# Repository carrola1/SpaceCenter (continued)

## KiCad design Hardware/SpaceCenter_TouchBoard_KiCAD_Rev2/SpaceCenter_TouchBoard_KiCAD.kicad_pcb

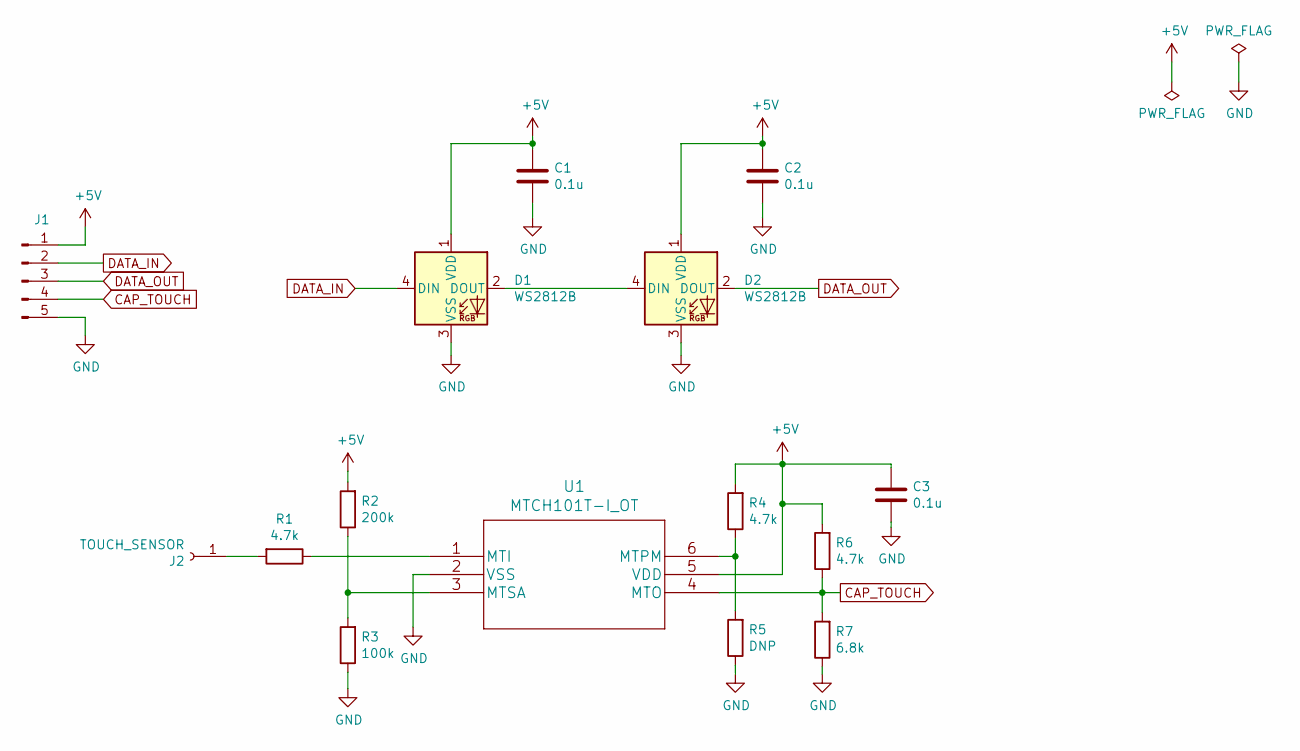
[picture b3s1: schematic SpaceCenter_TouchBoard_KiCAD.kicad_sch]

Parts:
C1, C2, C3: 0.1u; C_0402_1005Metric_Pad0.74x0.62mm_HandSolder
D1, D2: WS2812B; LED_WS2812B_PLCC4_5.0x5.0mm_P3.2mm
J1: Conn_01x05_Male; JST_SH_BM05B-SRSS-TB_1x05-1MP_P1.00mm_Vertical
J2: TOUCH_SENSOR; SolderWirePad_1x01_SMD_5x10mm
R1, R4, R6: 4.7k; R_0402_1005Metric_Pad0.72x0.64mm_HandSolder
R2: 200k; R_0402_1005Metric_Pad0.72x0.64mm_HandSolder
R3: 100k; R_0402_1005Metric_Pad0.72x0.64mm_HandSolder
R5: DNP; R_0402_1005Metric_Pad0.72x0.64mm_HandSolder
R7: 6.8k; R_0402_1005Metric_Pad0.72x0.64mm_HandSolder
U1: MTCH101T-I_OT; MTCH101T-I&slash_OT

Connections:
+5V: C1.1, C2.1, C3.1, D1.1 (VDD), D2.1 (VDD), J1.1, R2.2, R4.2, R6.2, U1.5 (VDD)
CAP_TOUCH: J1.4, R6.1, R7.2, U1.4 (MTO)
DATA_IN: D1.4 (DIN), J1.2
DATA_OUT: D2.2 (DOUT), J1.3
GND: C1.2, C2.2, C3.2, D1.3 (VSS), D2.3 (VSS), J1.5, R3.1, R5.1, R7.1, U1.2 (VSS)
unnamed: D1.2 (DOUT), D2.4 (DIN)
unnamed: J2.1, R1.2
unnamed: R1.1, U1.1 (MTI)
unnamed: R2.1, R3.2, U1.3 (MTSA)
unnamed: R4.1, R5.2, U1.6 (MTPM)

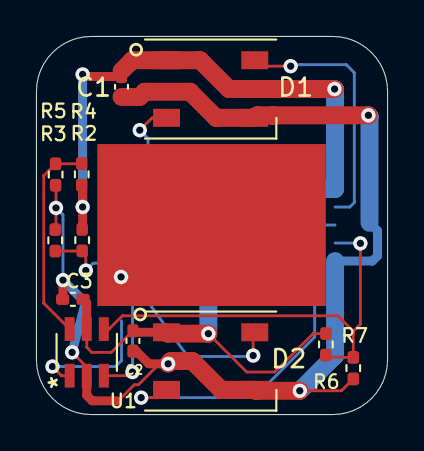
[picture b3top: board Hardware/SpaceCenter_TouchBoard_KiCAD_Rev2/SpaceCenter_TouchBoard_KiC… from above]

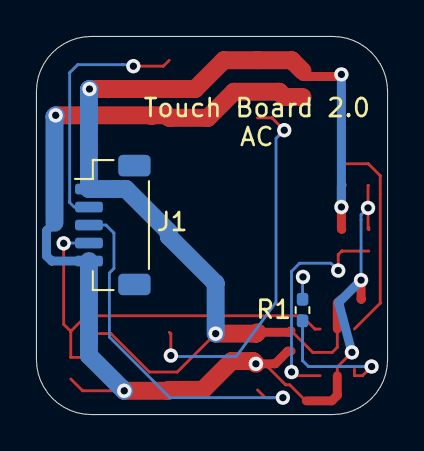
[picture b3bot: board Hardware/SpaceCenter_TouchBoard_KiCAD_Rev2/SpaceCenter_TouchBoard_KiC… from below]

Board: 2 copper layers, 19.5 x 21.0 mm, 15 parts (2 on the bottom side), 10 nets.

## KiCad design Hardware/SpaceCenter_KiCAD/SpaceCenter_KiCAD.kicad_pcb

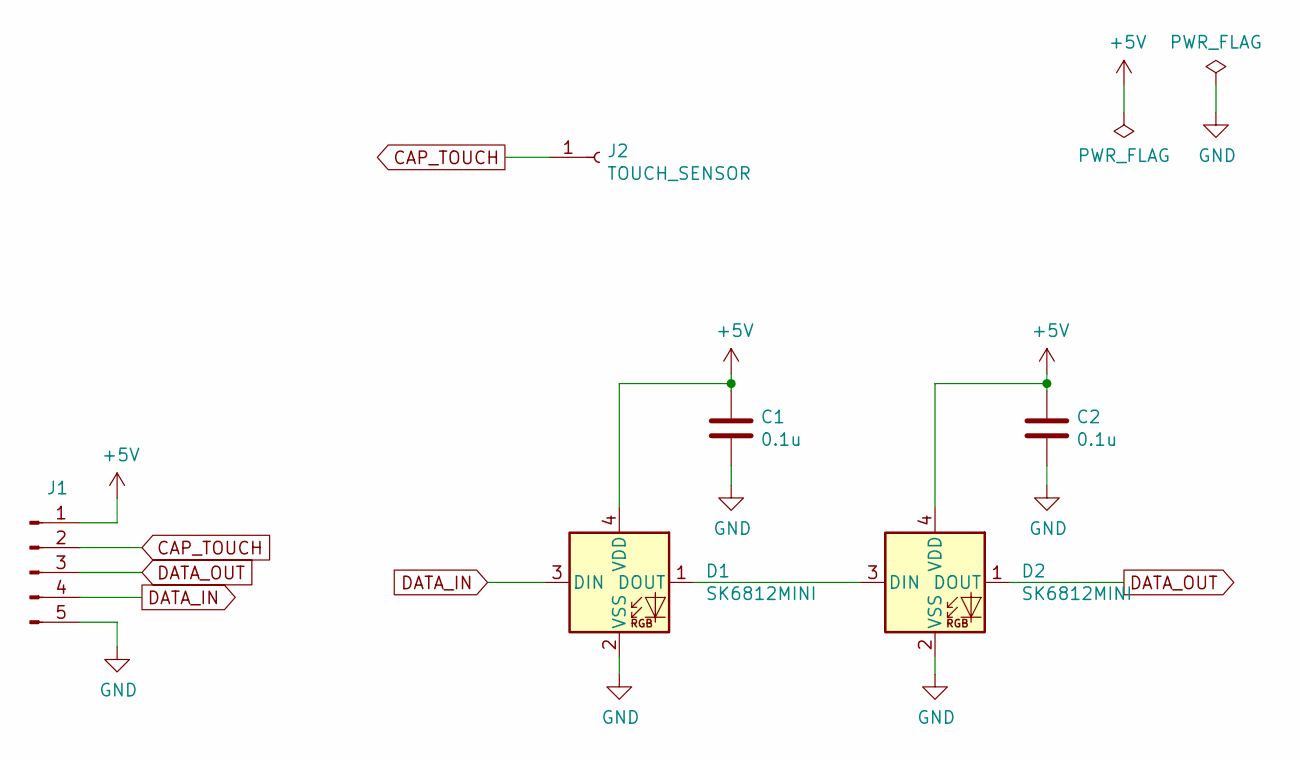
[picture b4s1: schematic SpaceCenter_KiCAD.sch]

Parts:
C1, C2: 0.1u; C_0603_1608Metric_Pad1.05x0.95mm_HandSolder
D1, D2: SK6812MINI; LED_SK6812MINI_PLCC4_3.5x3.5mm_P1.75mm
J1: Conn_01x05_Male; JST_SH_SM05B-SRSS-TB_1x05-1MP_P1.00mm_Horizontal
J2: TOUCH_SENSOR; SolderWirePad_1x01_SMD_5x10mm

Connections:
+5V: C1.1, C2.1, D1.4 (VDD), D2.4 (VDD), J1.1
CAP_TOUCH: J1.2, J2.1
DATA_IN: D1.3 (DIN), J1.4
DATA_OUT: D2.1 (DOUT), J1.3
GND: C1.2, C2.2, D1.2 (VSS), D2.2 (VSS), J1.5
unnamed: D1.1 (DOUT), D2.3 (DIN)

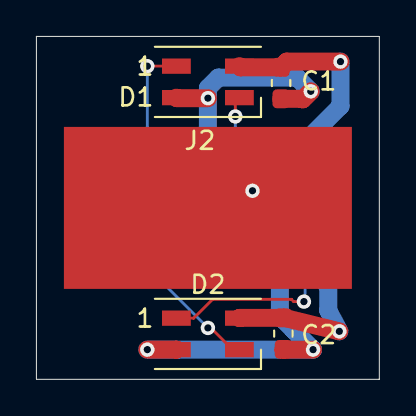
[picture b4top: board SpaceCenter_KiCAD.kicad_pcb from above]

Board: 2 copper layers, 19.1 x 19.1 mm, 6 parts (1 on the bottom side), 6 nets.

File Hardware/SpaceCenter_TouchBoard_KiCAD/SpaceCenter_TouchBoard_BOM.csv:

Item,Ref Des,Quantity,Part #,Digi-key Part #,Value/Description,Package,Type,Digi-key Cost
1,J1,1,DO NOT POPULATE,DO NOT POPULATE,Conn_01x05_Male,JST_SH_BM05B-SRSS-TB_1x05-1MP_P1.00mm_Vertical,SMD,
2,J2,1,DO NOT POPULATE,DO NOT POPULATE,Cap touch sensor,SolderWirePad_1x01_SMD_5x10mm,N/A,
3,"C1,C2",2,Basic,N/A,Ceramic 0.1u 50V +/-10% or better,C_0603_1608Metric_Pad1.05x0.95mm_HandSolder,SMD,
4,"D1,D2",2,SK6812,1528-1104-ND (qty 10),Serial Addressable RGB LED,LED_SK6812_PLCC4_5.0x5.0mm_P3.2mm,SMD,4.5

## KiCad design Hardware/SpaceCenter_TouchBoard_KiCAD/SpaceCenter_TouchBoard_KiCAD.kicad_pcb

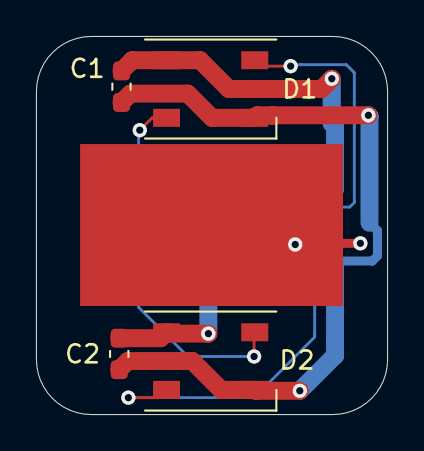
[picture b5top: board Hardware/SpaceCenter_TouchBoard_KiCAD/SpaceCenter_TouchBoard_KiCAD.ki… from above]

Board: 2 copper layers, 19.5 x 21.0 mm, 6 parts (1 on the bottom side), 6 nets.

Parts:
C1, C2: 0.1u; C_0603_1608Metric_Pad1.05x0.95mm_HandSolder
D1, D2: SK6812; LED_SK6812_PLCC4_5.0x5.0mm_P3.2mm
J1: Conn_01x05_Male; JST_SH_BM05B-SRSS-TB_1x05-1MP_P1.00mm_Vertical
J2: TOUCH_SENSOR; SolderWirePad_1x01_SMD_5x10mm

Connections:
+5V: C1.1, C2.1, D1.3, D2.3, J1.1
CAP_TOUCH: J1.4, J2.1
DATA_IN: D1.2, J1.2
DATA_OUT: D2.4, J1.3
GND: C1.2, C2.2, D1.1, D2.1, J1.5
unnamed: D1.4, D2.2

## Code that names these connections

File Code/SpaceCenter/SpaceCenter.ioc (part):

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Mcu.Name=STM32L072V(B-Z)Tx
Mcu.Package=LQFP100
Mcu.UserName=STM32L072VBTx
PA1.GPIOParameters=GPIO_Label
PA1.GPIO_Label=TOUCH_STAR_3
PA1.Signal=GPIO_Input
PA10.GPIOParameters=GPIO_Label
PA10.GPIO_Label=TOUCH_STAR_18
PA10.Signal=GPIO_Input
PA11.GPIOParameters=GPIO_Label
PA11.GPIO_Label=TOUCH_STAR_19
PA11.Signal=GPIO_Input
PA12.GPIOParameters=GPIO_Label
PA12.GPIO_Label=TOUCH_STAR_20
PA12.Signal=GPIO_Input
PA13.Mode=Serial_Wire
PA13.Signal=SYS_SWDIO
PA14.Mode=Serial_Wire
PA14.Signal=SYS_SWCLK
PA15.GPIOParameters=GPIO_Label
PA15.GPIO_Label=SD_SPI1_CS_N
PA15.Signal=GPIO_Output
PA2.GPIOParameters=GPIO_Label
PA2.GPIO_Label=TOUCH_STAR_4
PA2.Signal=GPIO_Input
PA3.GPIOParameters=GPIO_Label
PA3.GPIO_Label=TOUCH_STAR_5
PA3.Signal=GPIO_Input
PA5.GPIOParameters=GPIO_Label
PA5.GPIO_Label=TOUCH_STAR_6
PA5.Signal=GPIO_Input
PA6.GPIOParameters=GPIO_Label
PA6.GPIO_Label=TOUCH_STAR_7
PA6.Signal=GPIO_Input
PA7.GPIOParameters=GPIO_Label
PA7.GPIO_Label=TOUCH_STAR_8
PA7.Signal=GPIO_Input
PB0.GPIOParameters=GPIO_Label
PB0.GPIO_Label=TOUCH_STAR_9
PB0.Signal=GPIO_Input
PB1.GPIOParameters=GPIO_Label
PB1.GPIO_Label=TOUCH_STAR_10
PB1.Signal=GPIO_Input
PB12.GPIOParameters=GPIO_Label
PB12.GPIO_Label=TOUCH_STAR_12
PB12.Signal=GPIO_Input
PB13.GPIOParameters=GPIO_Label
PB13.GPIO_Label=TOUCH_STAR_13
PB13.Signal=GPIO_Input
PB14.GPIOParameters=GPIO_Label
PB14.GPIO_Label=TOUCH_STAR_14
PB14.Signal=GPIO_Input
PB15.GPIOParameters=GPIO_Speed,GPIO_Label
PB15.GPIO_Label=I2S_SPI2_SD
PB15.GPIO_Speed=GPIO_SPEED_FREQ_VERY_HIGH
PB15.Mode=Half_Duplex_Master
PB15.Signal=I2S2_SD
PB2.GPIOParameters=GPIO_Label
PB2.GPIO_Label=TOUCH_STAR_11
PB2.Signal=GPIO_Input
PB4.GPIOParameters=GPIO_Label
PB4.GPIO_Label=TOUCH_STAR_21
PB4.Signal=GPIO_Input
PB6.GPIOParameters=GPIO_Label
PB6.GPIO_Label=TOUCH_STAR_22
PB6.Signal=GPIO_Input
PB7.GPIOParameters=GPIO_Label
PB7.GPIO_Label=TOUCH_STAR_23
PB7.Signal=GPIO_Input
PC0.GPIOParameters=GPIO_Label
PC0.GPIO_Label=TOUCH_G7_1_SAMP
PC0.Signal=TSC_G7_IO1
PC1.GPIOParameters=GPIO_Label
PC1.GPIO_Label=TOUCH_STAR_0
PC1.Signal=GPIO_Input
PC13.GPIOParameters=GPIO_Label
PC13.GPIO_Label=BUTTON_R
PC13.Signal=GPIO_Input
PC14-OSC32_IN.GPIOParameters=GPIO_Label
PC14-OSC32_IN.GPIO_Label=BUTTON_LED_R
PC14-OSC32_IN.Signal=GPIO_Output
PC2.GPIOParameters=GPIO_Label
PC2.GPIO_Label=TOUCH_STAR_1
PC2.Signal=GPIO_Input
PC3.GPIOParameters=GPIO_Label
PC3.GPIO_Label=TOUCH_STAR_2
PC3.Signal=GPIO_Input
PC7.GPIOParameters=GPIO_Label
PC7.GPIO_Label=TOUCH_STAR_15
PC7.Signal=GPIO_Input
PC8.GPIOParameters=GPIO_Label
PC8.GPIO_Label=TOUCH_STAR_16
PC8.Signal=GPIO_Input
PC9.GPIOParameters=GPIO_Label
PC9.GPIO_Label=TOUCH_STAR_17
PC9.Signal=GPIO_Input
PD0.GPIOParameters=GPIO_Speed,GPIO_Label
PD0.GPIO_Label=I2S_SPI2_WS
PD0.GPIO_Speed=GPIO_SPEED_FREQ_VERY_HIGH
PD0.Mode=Half_Duplex_Master
PD0.Signal=I2S2_WS
PD1.GPIOParameters=GPIO_Speed,GPIO_Label
PD1.GPIO_Label=I2S_SPI2_CK
PD1.GPIO_Speed=GPIO_SPEED_FREQ_VERY_HIGH
PD1.Mode=Half_Duplex_Master
PD1.Signal=I2S2_CK
PD10.GPIOParameters=GPIO_Label
PD10.GPIO_Label=AUDIO_SD_N_L
PD10.Signal=GPIO_Output
PD11.GPIOParameters=GPIO_Label,GPIO_ModeDefaultOutputPP
PD11.GPIO_Label=AUDIO_SD_N_R
PD11.GPIO_ModeDefaultOutputPP=GPIO_MODE_OUTPUT_OD
PD11.Signal=GPIO_Output
PD15.GPIOParameters=GPIO_Label
PD15.GPIO_Label=MODE_SW
PD15.Signal=GPIO_Input
PE11.GPIOParameters=GPIO_Label
PE11.GPIO_Label=NEOPIX_ROCKET_L
PE11.Signal=S_TIM2_CH3
PE12.GPIOParameters=GPIO_Label
PE12.GPIO_Label=NEOPIX_ROCKET_R
PE12.Signal=S_TIM2_CH4
PE13.GPIOParameters=GPIO_Label
PE13.GPIO_Label=SD_SPI1_SCK
PE13.Mode=Full_Duplex_Master
PE13.Signal=SPI1_SCK
PE14.GPIOParameters=GPIO_Label
PE14.GPIO_Label=SD_SPI1_MISO
PE14.Mode=Full_Duplex_Master
PE14.Signal=SPI1_MISO
PE15.GPIOParameters=GPIO_Label
PE15.GPIO_Label=SD_SPI1_MOSI
PE15.Mode=Full_Duplex_Master
PE15.Signal=SPI1_MOSI
PE4.GPIOParameters=GPIO_Label
PE4.GPIO_Label=BUTTON_L
PE4.Signal=GPIO_Input
PE5.GPIOParameters=GPIO_Label
PE5.GPIO_Label=BUTTON_LED_L
PE5.Signal=GPIO_Output
PE7.GPIOParameters=GPIO_Label
PE7.GPIO_Label=SD_DET_A
PE7.Signal=GPIO_Input
PE8.GPIOParameters=GPIO_Label
PE8.GPIO_Label=SD_DET_B
PE8.Signal=GPIO_Input
PE9.GPIOParameters=GPIO_Label
PE9.GPIO_Label=NEOPIX_STARS
PE9.Signal=S_TIM2_CH1
PH10.GPIOParameters=GPIO_Label
PH10.GPIO_Label=TEST_LED
PH10.Signal=GPIO_Output
RCC.HSE_VALUE=8000000
RCC.SYSCLKFreq_VALUE=32000000
RCC.SYSCLKSource=RCC_SYSCLKSOURCE_PLLCLK
board=custom

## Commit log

2020-08-17 Nucleo project detects touch on breadboard wire
2021-02-16 Working on converting Nucleo project to C++
2021-02-18 NucleoTest_CPP project working with NeoPixels.
2021-02-19 Touch sensing working for Nucleo_CPP project.
2021-03-03 Updated Touch Board with new connector
2021-03-19 Debug LED functional. SD Card is communicating. DMA is functional. Getting FDISK_ERROR during mount.
2021-03-22 Audio / SD Card Working
2021-04-19 Touch control working with single channel.
2021-04-22 Fixed NeoPixel incorrect color issue. Updated touch thresholds based on testing with actual environment.
2021-04-26 Added sparkle method
2021-05-04 TouchBoard updated and ordered
2021-05-17 Updated HLA BOM and exported TouchBoard 3D files
2021-06-10 Adding rocket prints. Added PWM driver support for rocket LEDs.
2021-08-10 All 48 LEDs working
    Had to remove DMA circular buffer and change to a one shot. Was not able to update the buffer quite fast enough to beat the DMA. Moving to a 48MHz clock would likely fix this.
2021-08-12 Made 3 touch banks of 8 channels each,
    IO1's, IO2', IO3's grouped together in banks. Channels are still in order of neopixels. Doesn't work too well.
2021-08-13 All touch channels functioning. Need to add offset mapping.
    Channel 0 is still more sensitive than the rest.
2021-09-03 All touch sensors working and mapped properly
    Made 3 touch groups that include 8 channels each, all 8 in different banks.
2021-09-09 Discrete touch sensor interface implemented
    Currently getting a build error (can't find function f_mount)
2021-09-09 Now building successfully
2021-09-12 Touch Board rev 2.0 Working Great
2021-10-01 Touch Board 2.0 Fab Files
2021-10-05 Converted wav_player to c++ object
2023-11-07 Picking this project up again
    Unsure what the changes are...
2023-11-14 v3 Touch Board Schematic
    Updated v3 schematic to use the AT42QT1010 touch sensor
2023-12-22 Adding LedButton class
2023-12-23 KiCAD Updates
2024-01-02 Adding RocketStream class
2024-01-03 RocketStream working
2024-01-04 Starting on star count game
2024-01-16 Adding I'm A Star
2024-01-17 I'm a Star fully working
2024-01-17 Merging state_machine branch
2024-01-31 Rocket stream working
2024-02-15 Rocket countdown working
2024-02-20 Rocket song working
2024-02-20 Stars during rocket song
2024-02-21 Adding star counting audio
2024-02-23 Inactivity timer implemented
